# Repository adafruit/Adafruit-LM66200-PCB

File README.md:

## Adafruit LM66200 Ideal Dual Diodes Breakout PCB

<a href="http://www.adafruit.com/products/5830"><br/>
Click here to purchase one from the Adafruit shop</a>

PCB files for the Adafruit LM66200 Ideal Dual Diodes Breakout. 

Format is EagleCAD schematic and board layout
* https://www.adafruit.com/product/5830

### Description

Most projects these days have multiple power supplies: say a battery or DC wall plug or USB for multiple powering options. Juggling these to have seamless hot-swap while avoiding back-powering is always a bit of a challenge: you want to keep things small, cheap, low power and of course reduce as much voltage drop as possible.

The Adafruit LM66200 Dual Ideal Diode breakout is a cute solution to dual supplies: it has back-voltage protection, and two 'ideal' diodes with RdsOn of 40 milliohms, support for 2.5A continuous draw and a separate enable input and status output.

Sure you could DIY the circuitry with multiple transistors, but this is compact and easy to use! Simply connect the two 2~5V power supplies to Vin1 and Vin2, the higher of the two will appear on Vout. Disable the output completely by pulling the On/Enable pin high. Check the Status pin, if desired, to see whether Vin1 or Vin2 is the selected supply.

To make it bread-board friendly, we've placed it on a small PCB with 6 x 0.1" breakout pads. The chip and a 1 Megaohm enable-pulldown is soldered on top. We include a bit of header, some light soldering is required to attach the header - or use free wiring if you want to insert it directly into a circuit.

### License

Adafruit invests time and resources providing this open source design, please support Adafruit and open-source hardware by purchasing products from [Adafruit](https://www.adafruit.com)!

Designed by Limor Fried/Ladyada for Adafruit Industries.

Creative Commons Attribution/Share-Alike, all text above must be included in any redistribution. 
See license.txt for additional details.

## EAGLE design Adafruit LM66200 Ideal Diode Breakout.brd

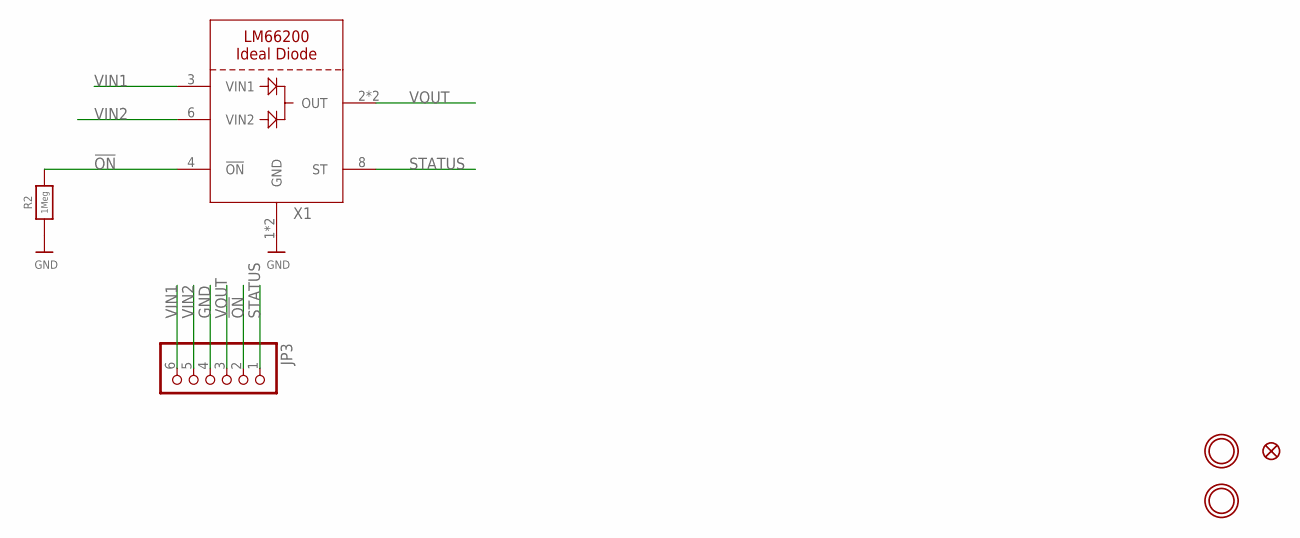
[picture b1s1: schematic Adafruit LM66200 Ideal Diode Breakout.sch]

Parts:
FID2: FIDUCIAL_1MM
JP3: HEADER-1X670MIL; 1X06_ROUND_70
R2: 1Meg; 0603-NO
U$1, U$9: MOUNTINGHOLE2.5; MOUNTINGHOLE_2.5_PLATED
X1: LM66200; SOT583

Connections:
!ON: JP3.2, R2.2, X1.4 (!ON)
GND: JP3.4, R2.1, X1.1 (GND), X1.5 (GND)
STATUS: JP3.1, X1.8 (ST)
VIN1: JP3.6, X1.3 (VIN1)
VIN2: JP3.5, X1.6 (VIN2)
VOUT: JP3.3, X1.2 (OUT), X1.7 (OUT)

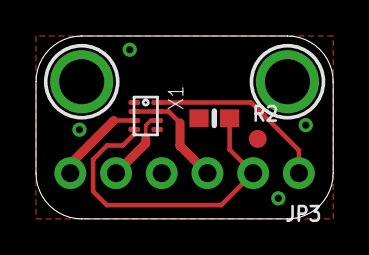
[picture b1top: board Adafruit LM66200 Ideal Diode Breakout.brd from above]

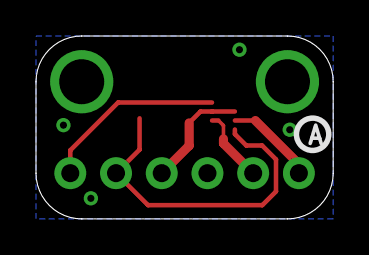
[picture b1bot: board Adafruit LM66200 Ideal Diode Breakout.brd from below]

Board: 2 copper layers, 16.5 x 10.2 mm, 18 parts (3 on the bottom side), 6 nets.

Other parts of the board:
PLABEL0: PLABEL0
PLABEL1: PLABEL1
PLABEL2: PLABEL2
PLABEL3: PLABEL3
PLABEL4: PLABEL4
PLABEL5: PLABEL5
PLABEL6: PLABEL6
PLABEL7: PLABEL7
PLABEL8: PLABEL8
PLABEL9: PLABEL9
PLABEL10: PLABEL10
U$10: PCBFEAT-REV-040

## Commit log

2023-11-02 cookiecutter output

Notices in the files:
parts and their libraries:
microbuilder: This work is placed in the public domain, and may be freely used for commercial and non-commercial work with the following conditions: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
